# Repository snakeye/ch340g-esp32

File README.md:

# CH340G programmer for ESP8266/ESP32

Programming device for ESP8266/ESP32 microcontrollers with proper BOOT/RST cirquitry and +3.3V power output.

More info in my blog [https://en.ovcharov.me/2019/08/16/ch340g-programmer-for-esp8266-esp32/](https://en.ovcharov.me/2019/08/16/ch340g-programmer-for-esp8266-esp32/).

## Update log

**Updated 2020/12/21** Added USB Type C connector and changed header pinout for compatibility with ESP01e

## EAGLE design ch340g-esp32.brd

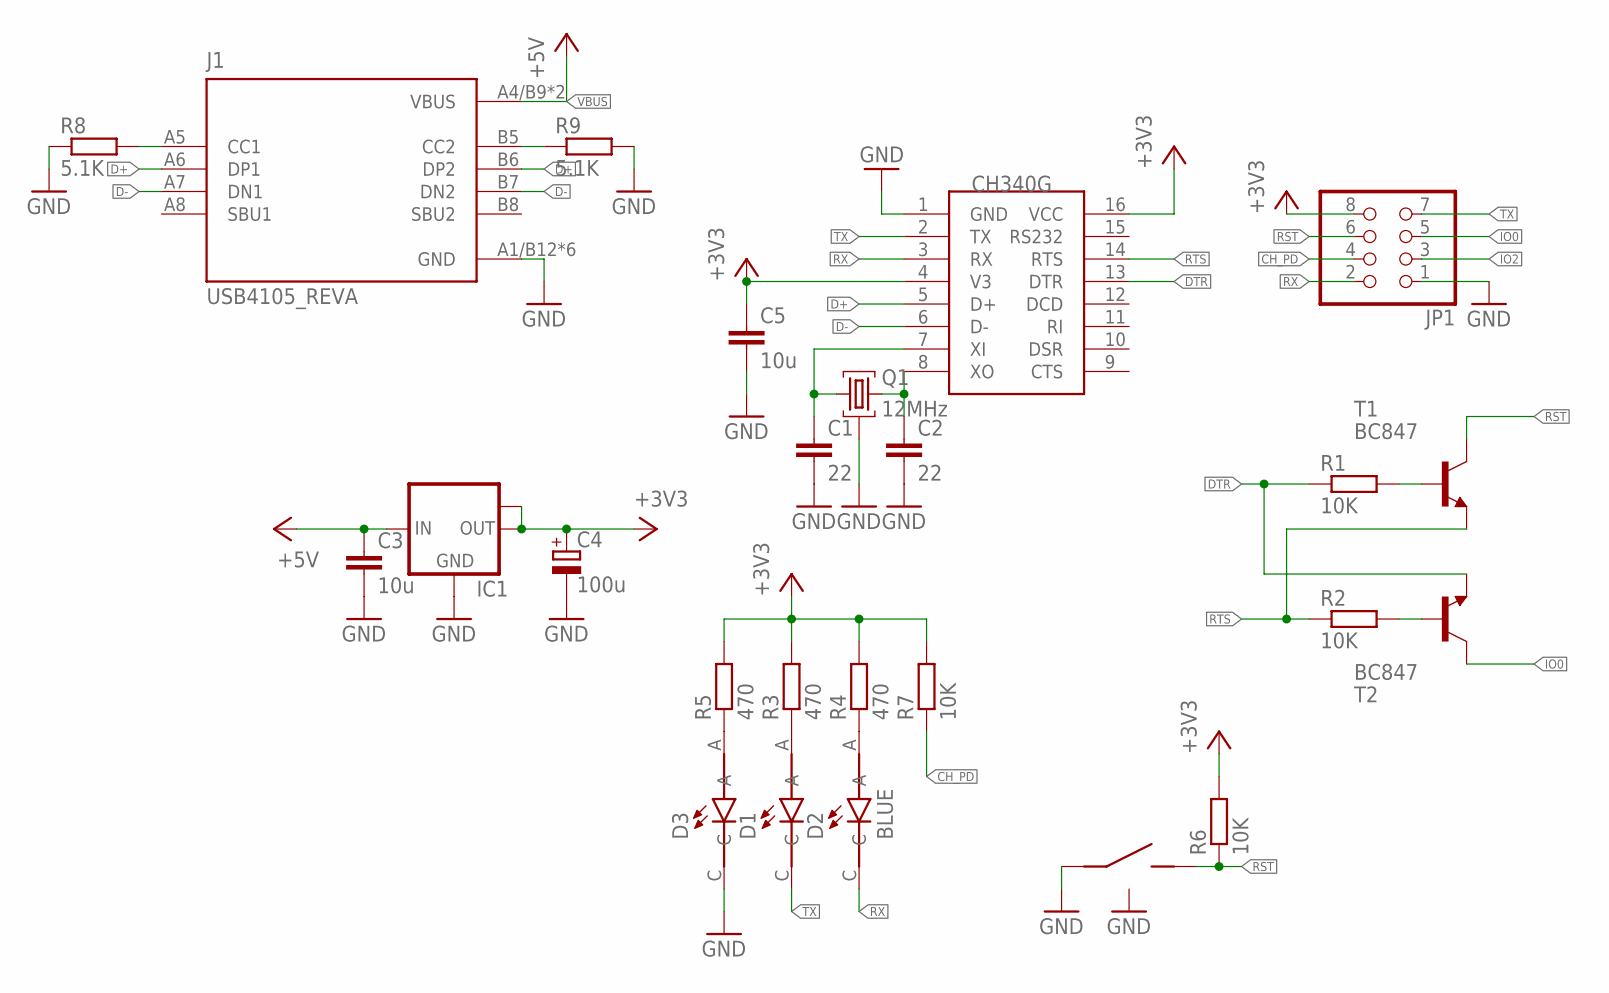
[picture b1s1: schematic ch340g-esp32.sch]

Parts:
BTN1: TS36CA-0.7; SMD
C1, C2: 22; C0603
C3, C5: 10u; C0603
C4: 100u; B/3528-21W
D1, D2: BLUE; LEDC2012X70N
D3: GREEN; LEDC2012X70N
IC1: LM1117MPX-3.3; SOT223
J1: USB4105_REVA; GCT_USB4105_REVA
JP1: PINHD-2X4; 2X04
Q1: 12MHz; SMD3225
R1, R2, R6, R7: 10K; R0603
R3, R4, R5: 470; R0603
R8, R9: 5.1K; R0603
T1, T2: BC847; SOT23
U1: CH340G; SOIC16

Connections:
+3V3: C4.+, C5.1, IC1.2 (OUT), IC1.TAB (OUT1), JP1.8, R3.2, R4.2, R5.2, R6.2, R7.2, U1.4 (V3), U1.16 (VCC)
CH_PD: JP1.4, R7.1
D+: J1.A6 (DP1), J1.B6 (DP2), U1.5 (D+)
D-: J1.A7 (DN1), J1.B7 (DN2), U1.6 (D-)
DTR: R1.1, T2.2 (E), U1.13 (DTR)
GND: BTN1.A (CASE), BTN1.B (CASE), BTN1.C, C1.2, C2.2, C3.2, C4.-, C5.2, D3.C, IC1.1 (GND), J1.A1/B12 (GND), J1.B1/A12 (GND), J1.G1 (GND), J1.G2 (GND), J1.G3 (GND), J1.G4 (GND), JP1.1, Q1.P$2 (CASE), Q1.P$4 (CASE), R8.1, R9.2, U1.1 (GND)
IO0: JP1.5, T2.3 (C)
IO2: JP1.3
unnamed: C2.1, Q1.P$3 (2), U1.8 (XO)
unnamed: C1.1, Q1.P$1 (1), U1.7 (XI)
unnamed: R1.2, T1.1 (B)
unnamed: R2.2, T2.1 (B)
unnamed: D1.A, R3.1
unnamed: D3.A, R5.1
unnamed: J1.A5 (CC1), R8.2
unnamed: J1.B5 (CC2), R9.1
unnamed: D2.A, R4.1
RST: BTN1.D, JP1.6, R6.1, T1.3 (C)
RTS: R2.1, T1.2 (E), U1.14 (RTS)
RX: D2.C, JP1.2, U1.3 (RX)
TX: D1.C, JP1.7, U1.2 (TX)
VBUS: C3.1, IC1.3 (IN), J1.A4/B9 (VBUS), J1.B4/A9 (VBUS)

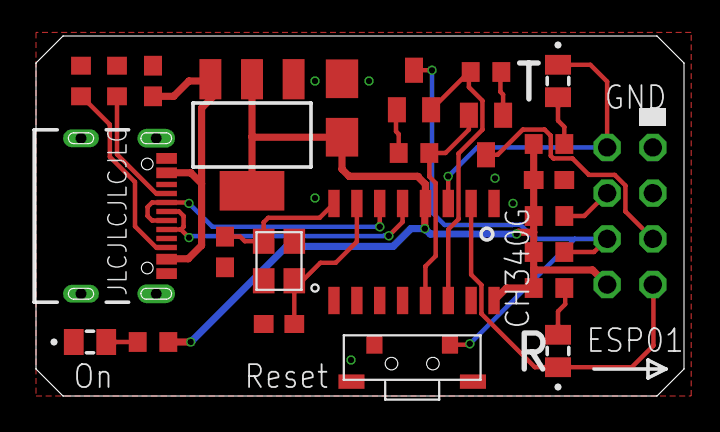
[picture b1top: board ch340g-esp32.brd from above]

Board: 2 copper layers, 36.0 x 20.0 mm, 25 parts (1 on the bottom side), 21 nets.

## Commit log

2019-07-28 rev1
2019-07-28 schematic pdf
2019-08-17 added images
2019-10-27 board update
2020-01-06 Fixed link in README.md
2020-01-06 Added schematics image to README.md
2020-01-06 Small update to README.md
2020-11-26 USB TypeC connector; Smaller board
2020-11-26 Production files
2020-12-03 Small improvements
2020-12-21 Readme update
2022-08-09 Added support for powering from USB Cable
2023-12-15 Add renovate.json
